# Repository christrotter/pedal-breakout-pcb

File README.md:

# Overview
A breakout pcb that helps make pedal wiring less nightmarish.  Intended to be used with these: https://github.com/christrotter/microswitch-pcb

I needed a cleaner way of wiring up my pedals, and now that I know how to make basic pcbs...well, for the price, hard to go back to janky prototyping boards.

Don't mind the renders, it's meant to utilize JST-XH horizontal connectors pointed inwards to minimize the room needed for cable routing space.
- This is meant to be super simple - just a breakout pcb
- TRRS PB-320A footprint wired up for full-duplex serial
- JST-XH 8-pin for your external indicator module
  - 2x buttons
  - LED in
  - +5V/GND
  - Reset
- 3x JST-XH 6-pin for MCU row/col, led, power/gnd, reset, serial, etc
- 1x 2-pin for reset
- 8x JST-XH 6-pin for button PCB connectivity
  - +5V/GND
  - LED IN/OUT
  - ROW & COL
- 8x JST-XH 4-pin for any internal LED necessities
  - +5V/GND
  - LED IN/OUT

I was going to do the whole nine yards and put in serial power protection and data esd, led signal up-convert, and more...but PCBA + shipping would end up being $60-80.  This design ended up being $19 shipped (_then an $8 coupon brought it down to $11 shipped_).

# Schematic

# PCB layout

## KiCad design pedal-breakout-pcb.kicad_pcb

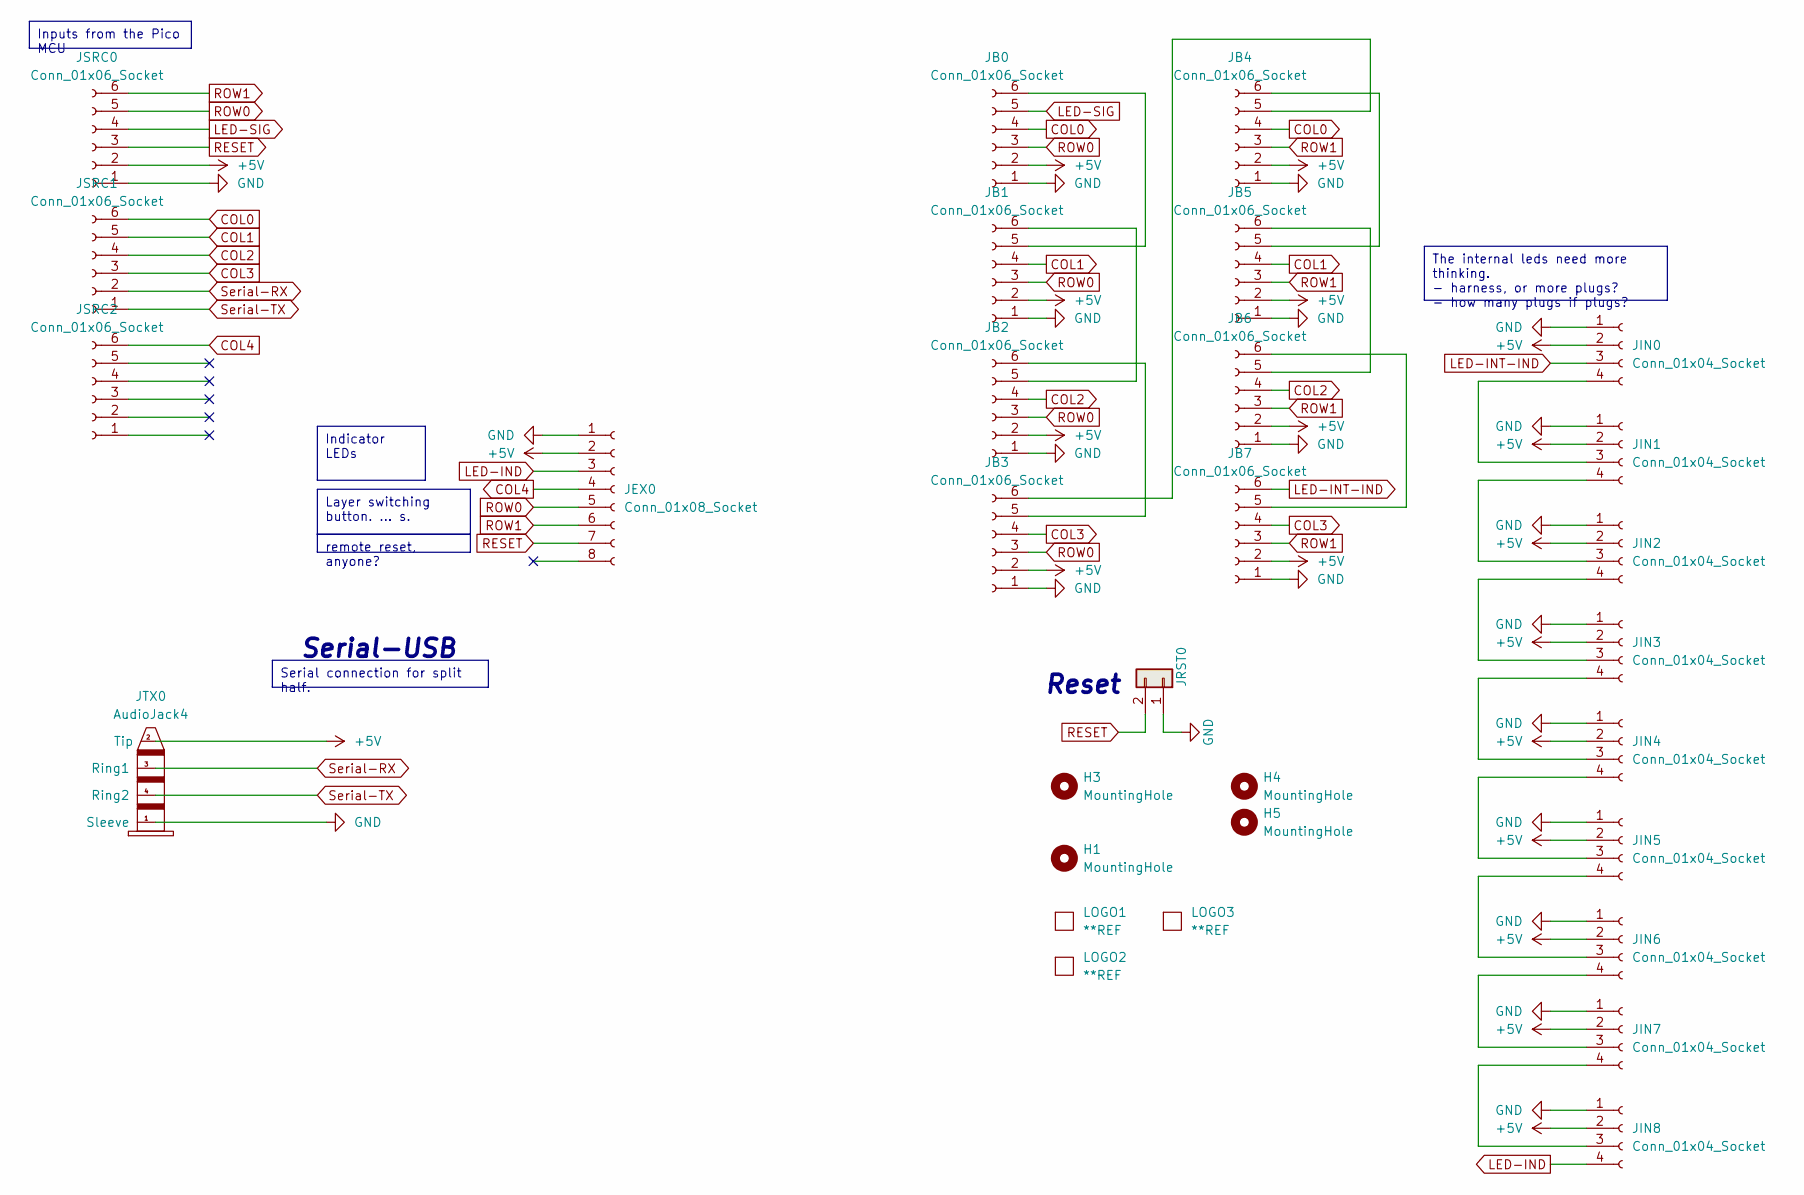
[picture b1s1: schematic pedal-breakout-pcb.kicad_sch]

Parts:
H1, H3: MountingHole; MountingHole_3.2mm_M3_Pad_Via
H4, H5: MountingHole; MountingHole_5mm
JB0, JB1, JB2, JB3, JB4, JB5, JB6, JB7: Conn_01x06_Socket; JST_XH_1x06_P2.50mm_Horizontal-CT
JEX0: Conn_01x08_Socket; JST_XH_1x08_P2.50mm_Horizontal-CT
JIN0, JIN1, JIN2, JIN3, JIN4, JIN5, JIN6, JIN7, JIN8: Conn_01x04_Socket; JST_XH_1x04_P2.50mm_Horizontal-CT
JRST0: Conn_01x02; JST_XH_S2B-XH-A_1x02_P2.50mm_Horizontal
JSRC0, JSRC1, JSRC2: Conn_01x06_Socket; JST_XH_1x06_P2.50mm_Horizontal-CT
JTX0: AudioJack4; PJ-320A
LOGO1, LOGO2: **REF; awesome-logo
LOGO3: **REF; pedalinator-qr-10mm

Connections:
+5V: JB0.2, JB1.2, JB2.2, JB3.2, JB4.2, JB5.2, JB6.2, JB7.2, JEX0.2, JIN0.2, JIN1.2, JIN2.2, JIN3.2, JIN4.2, JIN5.2, JIN6.2, JIN7.2, JIN8.2, JSRC0.2, JTX0.2 (Tip)
COL0: JB0.4, JB4.4, JSRC1.6
COL1: JB1.4, JB5.4, JSRC1.5
COL2: JB2.4, JB6.4, JSRC1.4
COL3: JB3.4, JB7.4, JSRC1.3
COL4: JEX0.4, JSRC2.6
GND: JB0.1, JB1.1, JB2.1, JB3.1, JB4.1, JB5.1, JB6.1, JB7.1, JEX0.1, JIN0.1, JIN1.1, JIN2.1, JIN3.1, JIN4.1, JIN5.1, JIN6.1, JIN7.1, JIN8.1, JRST0.1, JSRC0.1, JTX0.1 (Sleeve)
LED-IND: JEX0.3, JIN8.4
LED-INT-IND: JB7.6, JIN0.3
LED-SIG: JB0.5, JSRC0.4
unnamed: JB0.6, JB1.5
unnamed: JB1.6, JB2.5
unnamed: JB2.6, JB3.5
unnamed: JB3.6, JB4.5
unnamed: JB4.6, JB5.5
unnamed: JB5.6, JB6.5
unnamed: JB6.6, JB7.5
unnamed: JIN0.4, JIN1.3
unnamed: JIN1.4, JIN2.3
unnamed: JIN2.4, JIN3.3
unnamed: JIN3.4, JIN4.3
unnamed: JIN4.4, JIN5.3
unnamed: JIN5.4, JIN6.3
unnamed: JIN6.4, JIN7.3
unnamed: JIN7.4, JIN8.3
RESET: JEX0.7, JRST0.2, JSRC0.3
ROW0: JB0.3, JB1.3, JB2.3, JB3.3, JEX0.5, JSRC0.5
ROW1: JB4.3, JB5.3, JB6.3, JB7.3, JEX0.6, JSRC0.6
Serial-RX: JSRC1.2, JTX0.3 (Ring1)
Serial-TX: JSRC1.1, JTX0.4 (Ring2)

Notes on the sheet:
Serial connection for split half.
The internal leds need more thinking. - harness, or more plugs? - how many plugs if plugs?
Layer switching button. ... s.
remote reset, anyone?
Inputs from the Pico MCU
Indicator LEDs
Reset
Serial-USB

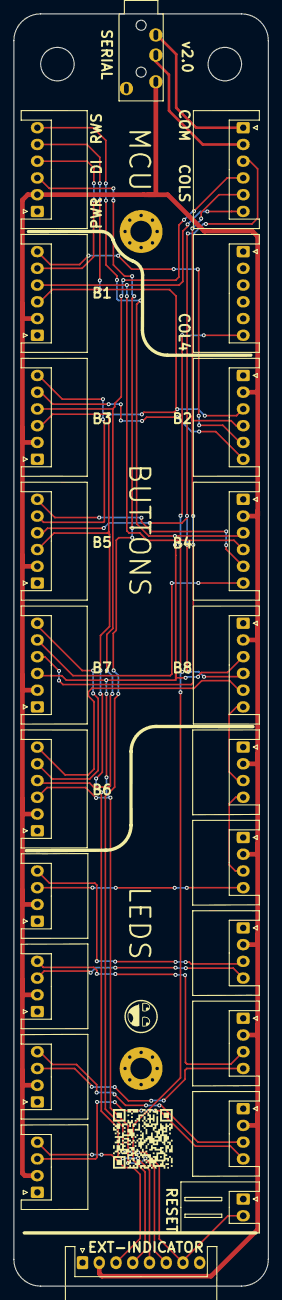
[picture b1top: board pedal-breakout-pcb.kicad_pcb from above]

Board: 2 copper layers, 38.0 x 190.0 mm, 30 parts (1 on the bottom side), 30 nets.

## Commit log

2024-08-17 adding gitignore
2024-08-17 adding project and step files
2024-08-17 updating readme
2024-08-17 adding images oops
2024-08-30 version2 files
